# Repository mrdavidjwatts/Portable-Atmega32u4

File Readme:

This board is still in development, please do not get it printed it may not work

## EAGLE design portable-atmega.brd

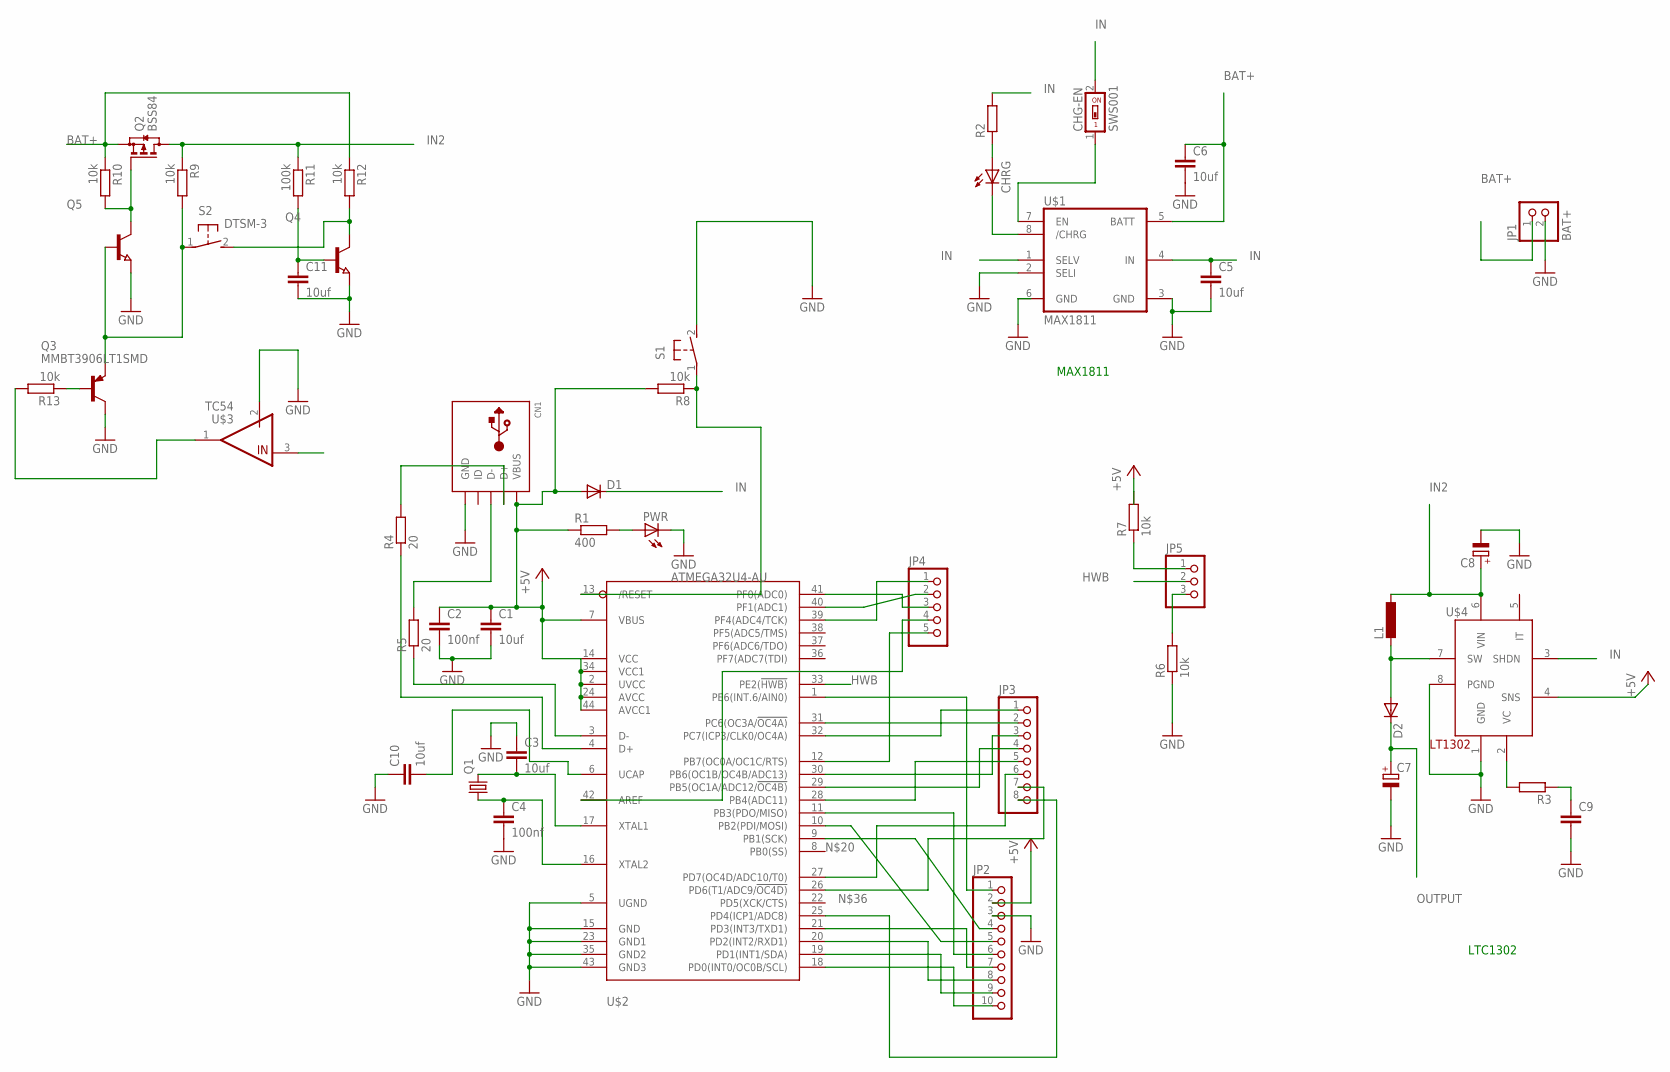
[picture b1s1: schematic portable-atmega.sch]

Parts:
C1, C3, C5, C6, C10, C11: 10uf; C1206
C2, C4: 100nf; C1206
C7, C8: CPOL-EUD; PANASONIC_D
C9: C-EUC1206; C1206
CHG-EN: SWS001; SMS-001
CHRG: LEDCHIPLED_1206; CHIPLED_1206
CN1: USBMINIB; USB-MINIB
D1, D2: DIODE-DO214AA; DO214AA
JP1: BAT+; 1X02
JP2: PINHD-1X10; 1X10
JP3: PINHD-1X8; 1X08
JP4: PINHD-1X5; 1X05
JP5: PINHD-1X3; 1X03
L1: DO3316P
PWR: LEDCHIPLED_1206; CHIPLED_1206
Q1: CRYSTALHC49S; HC49/S
Q2: BSS84; SOT23
Q3: MMBT3906LT1SMD; SOT23-BEC
Q4, Q5: NPN-TRANSISTOR_SOT23; SOT23
R1: 400; R1206
R2, R3: R-EU_R1206; R1206
R4, R5: 20; R1206
R6, R7, R8, R9, R13: 10k; R0805
R10, R12: 10k; R1206
R11: 100k; R0805
S1: 31-XXSKINNY; B3F-31XX-SKINNIER
S2: DTSM-3
U$1: MAX1811; SO08
U$2: ATMEGA32U4-AU; TQFP44
U$3: TC54; SOT23-3
U$4: LT1302SO8; SO08

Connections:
+5V: C1.1, C2.1, CN1.VBUS, D1.A, JP2.2, R1.1, R7.2, R8.2, U$2.2 (UVCC), U$2.7 (VBUS), U$2.14 (VCC), U$2.24 (AVCC), U$2.34 (VCC1), U$2.44 (AVCC1), U$4.4 (SNS)
BAT+: C6.1, JP1.1, Q2.2 (S), R10.1, R12.1, U$1.5 (BATT), U$3.3 (VIN)
GND: C1.2, C2.2, C3.1, C4.2, C5.2, C6.2, C7.-, C8.-, C9.2, C10.1, C11.2, CN1.GND, JP1.2, JP2.3, PWR.C, Q3.C, Q4.2 (E), Q5.2 (E), R6.1, S1.2 (S), U$1.2 (SELI), U$1.3 (GND), U$1.6 (GND), U$2.5 (UGND), U$2.15 (GND), U$2.23 (GND1), U$2.35 (GND2), U$2.43 (GND3), U$3.2 (VSS), U$4.1 (GND), U$4.8 (PGND)
HWB: JP5.2, U$2.33 (PE2(!HWB))
IN: C5.1, CHG-EN.2, D1.C, R2.2, U$1.1 (SELV), U$1.4 (IN), U$4.3 (SHDN)
IN2: C8.+, L1.2, Q2.3 (D), R9.1, R11.1, U$4.6 (VIN)
unnamed: PWR.A, R1.2
unnamed: CN1.D-, R5.2
unnamed: C4.1, Q1.1, U$2.16 (XTAL2)
unnamed: CHRG.C, U$1.8 (/CHRG)
unnamed: CHRG.A, R2.1
unnamed: C3.2, Q1.2, U$2.17 (XTAL1)
unnamed: CHG-EN.1, U$1.7 (EN)
unnamed: D2.A, L1.1, U$4.7 (SW)
unnamed: R4.1, U$2.4 (D+)
unnamed: CN1.D+, R4.2
unnamed: R5.1, U$2.3 (D-)
unnamed: C9.1, R3.1
unnamed: R3.2, U$4.2 (VC)
unnamed: C10.2, U$2.6 (UCAP)
unnamed: JP2.10, U$2.18 (PD0(INT0/OC0B/SCL))
unnamed: JP2.9, U$2.19 (PD1(INT1/SDA))
unnamed: JP2.8, U$2.20 (PD2(INT2/RXD1))
unnamed: JP2.7, U$2.21 (PD3(INT3/TXD1))
unnamed: JP2.1, U$2.1 (PE6(INT.6/AIN0))
unnamed: JP2.4, U$2.9 (PB1(SCK))
unnamed: JP2.5, U$2.10 (PB2(PDI/MOSI))
unnamed: JP2.6, U$2.11 (PB3(PDO/MISO))
unnamed: JP4.4, U$2.42 (AREF)
unnamed: JP4.3, U$2.41 (PF0(ADC0))
unnamed: JP4.2, U$2.40 (PF1(ADC1))
unnamed: JP4.1, U$2.39 (PF4(ADC4/TCK))
unnamed: JP5.3, R6.2
unnamed: JP3.1, U$2.32 (PC7(ICP3/CLK0/OC4A))
unnamed: JP3.2, U$2.31 (PC6(OC3A/!OC4A))
unnamed: JP3.3, U$2.30 (PB6(OC1B/OC4B/ADC13))
unnamed: JP5.1, R7.1
unnamed: R8.1, S1.1, U$2.13 (/RESET)
unnamed: JP3.4, U$2.29 (PB5(OC1A/ADC12/!OC4B))
unnamed: JP3.5, U$2.28 (PB4(ADC11))
unnamed: JP3.6, U$2.27 (PD7(OC4D/ADC10/T0))
unnamed: JP3.7, U$2.26 (PD6(T1/ADC9/!OC4D))
unnamed: JP3.8, U$2.25 (PD4(ICP1/ADC8))
unnamed: JP4.5, U$2.12 (PB7(OC0A/OC1C/RTS))
unnamed: Q2.1 (G), Q5.3 (C), R10.2
unnamed: Q3.E, Q5.1 (B), R9.2, S2.1
unnamed: C11.1, Q4.1 (B), R11.2
unnamed: Q4.3 (C), R12.2, S2.2
unnamed: R13.2, U$3.1 (VOUT)
unnamed: Q3.B, R13.1
OUTPUT: C7.+, D2.C

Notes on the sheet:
LTC1302
MAX1811

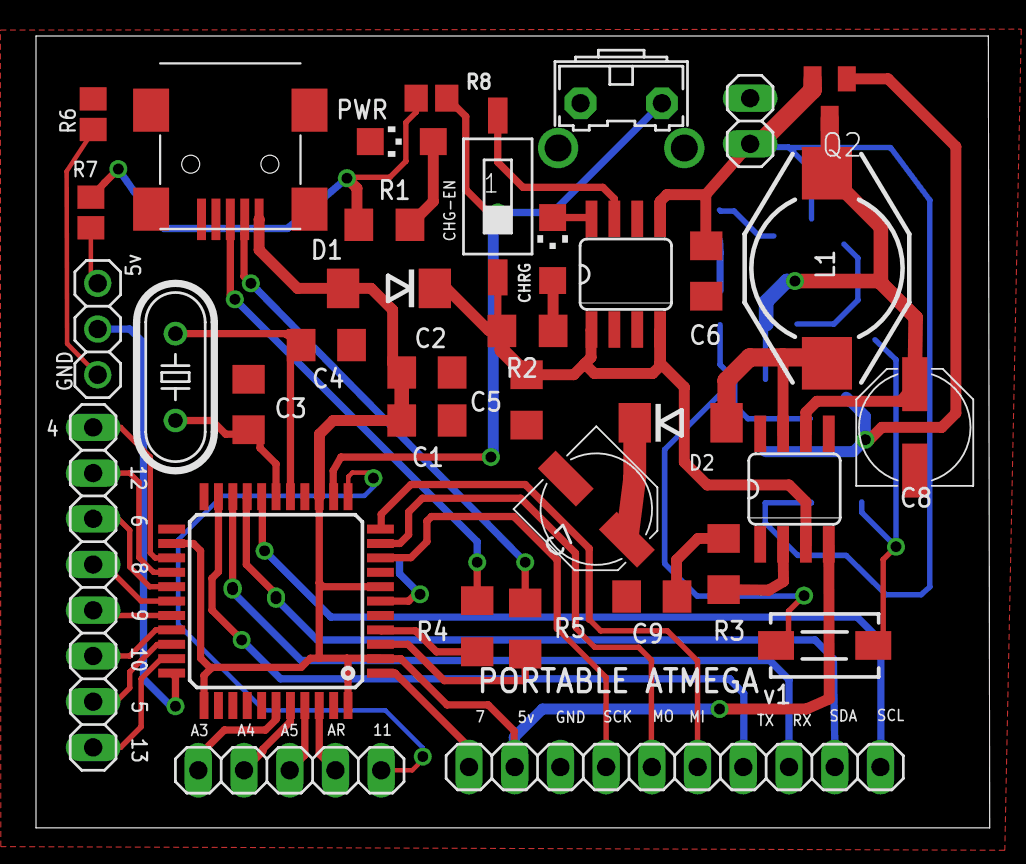
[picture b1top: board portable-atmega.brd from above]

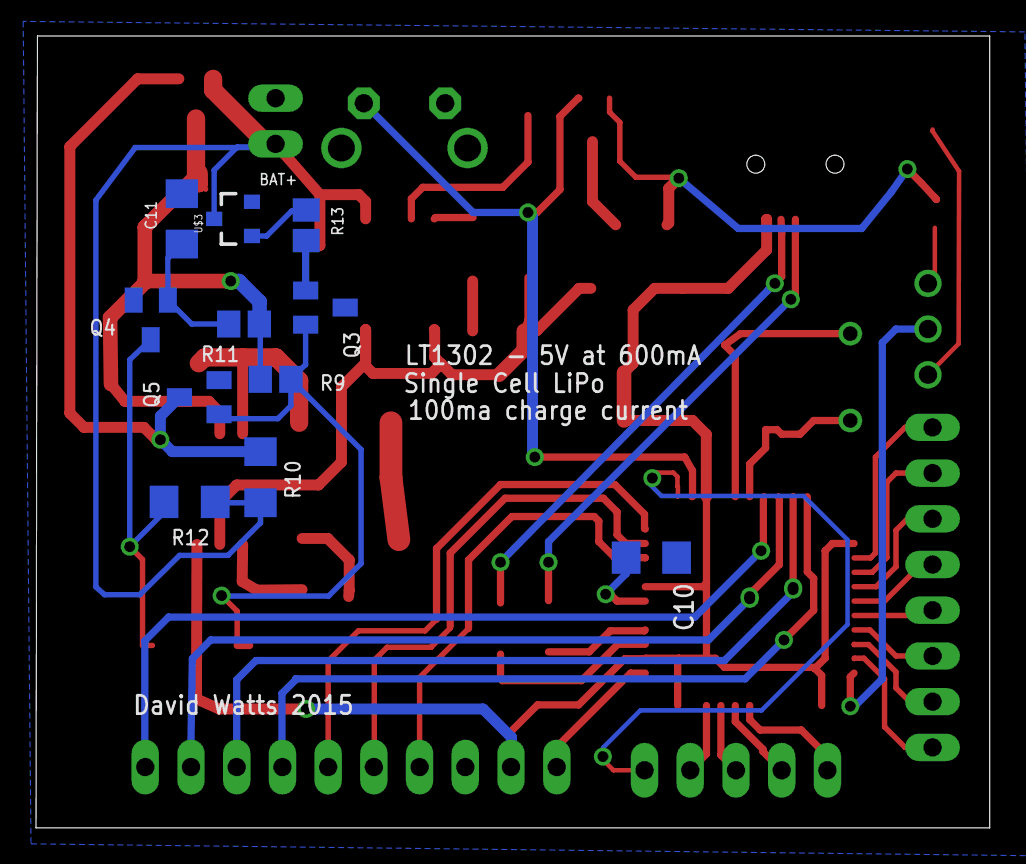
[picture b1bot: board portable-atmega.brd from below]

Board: 2 copper layers, 53.0 x 44.0 mm, 47 parts (11 on the bottom side), 51 nets.

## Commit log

2015-08-05 :boom::camel: Added .gitattributes
2015-08-05 Board File and Schematic
2015-08-10 Updated Schematic and BRD
2015-09-16 Read this first
